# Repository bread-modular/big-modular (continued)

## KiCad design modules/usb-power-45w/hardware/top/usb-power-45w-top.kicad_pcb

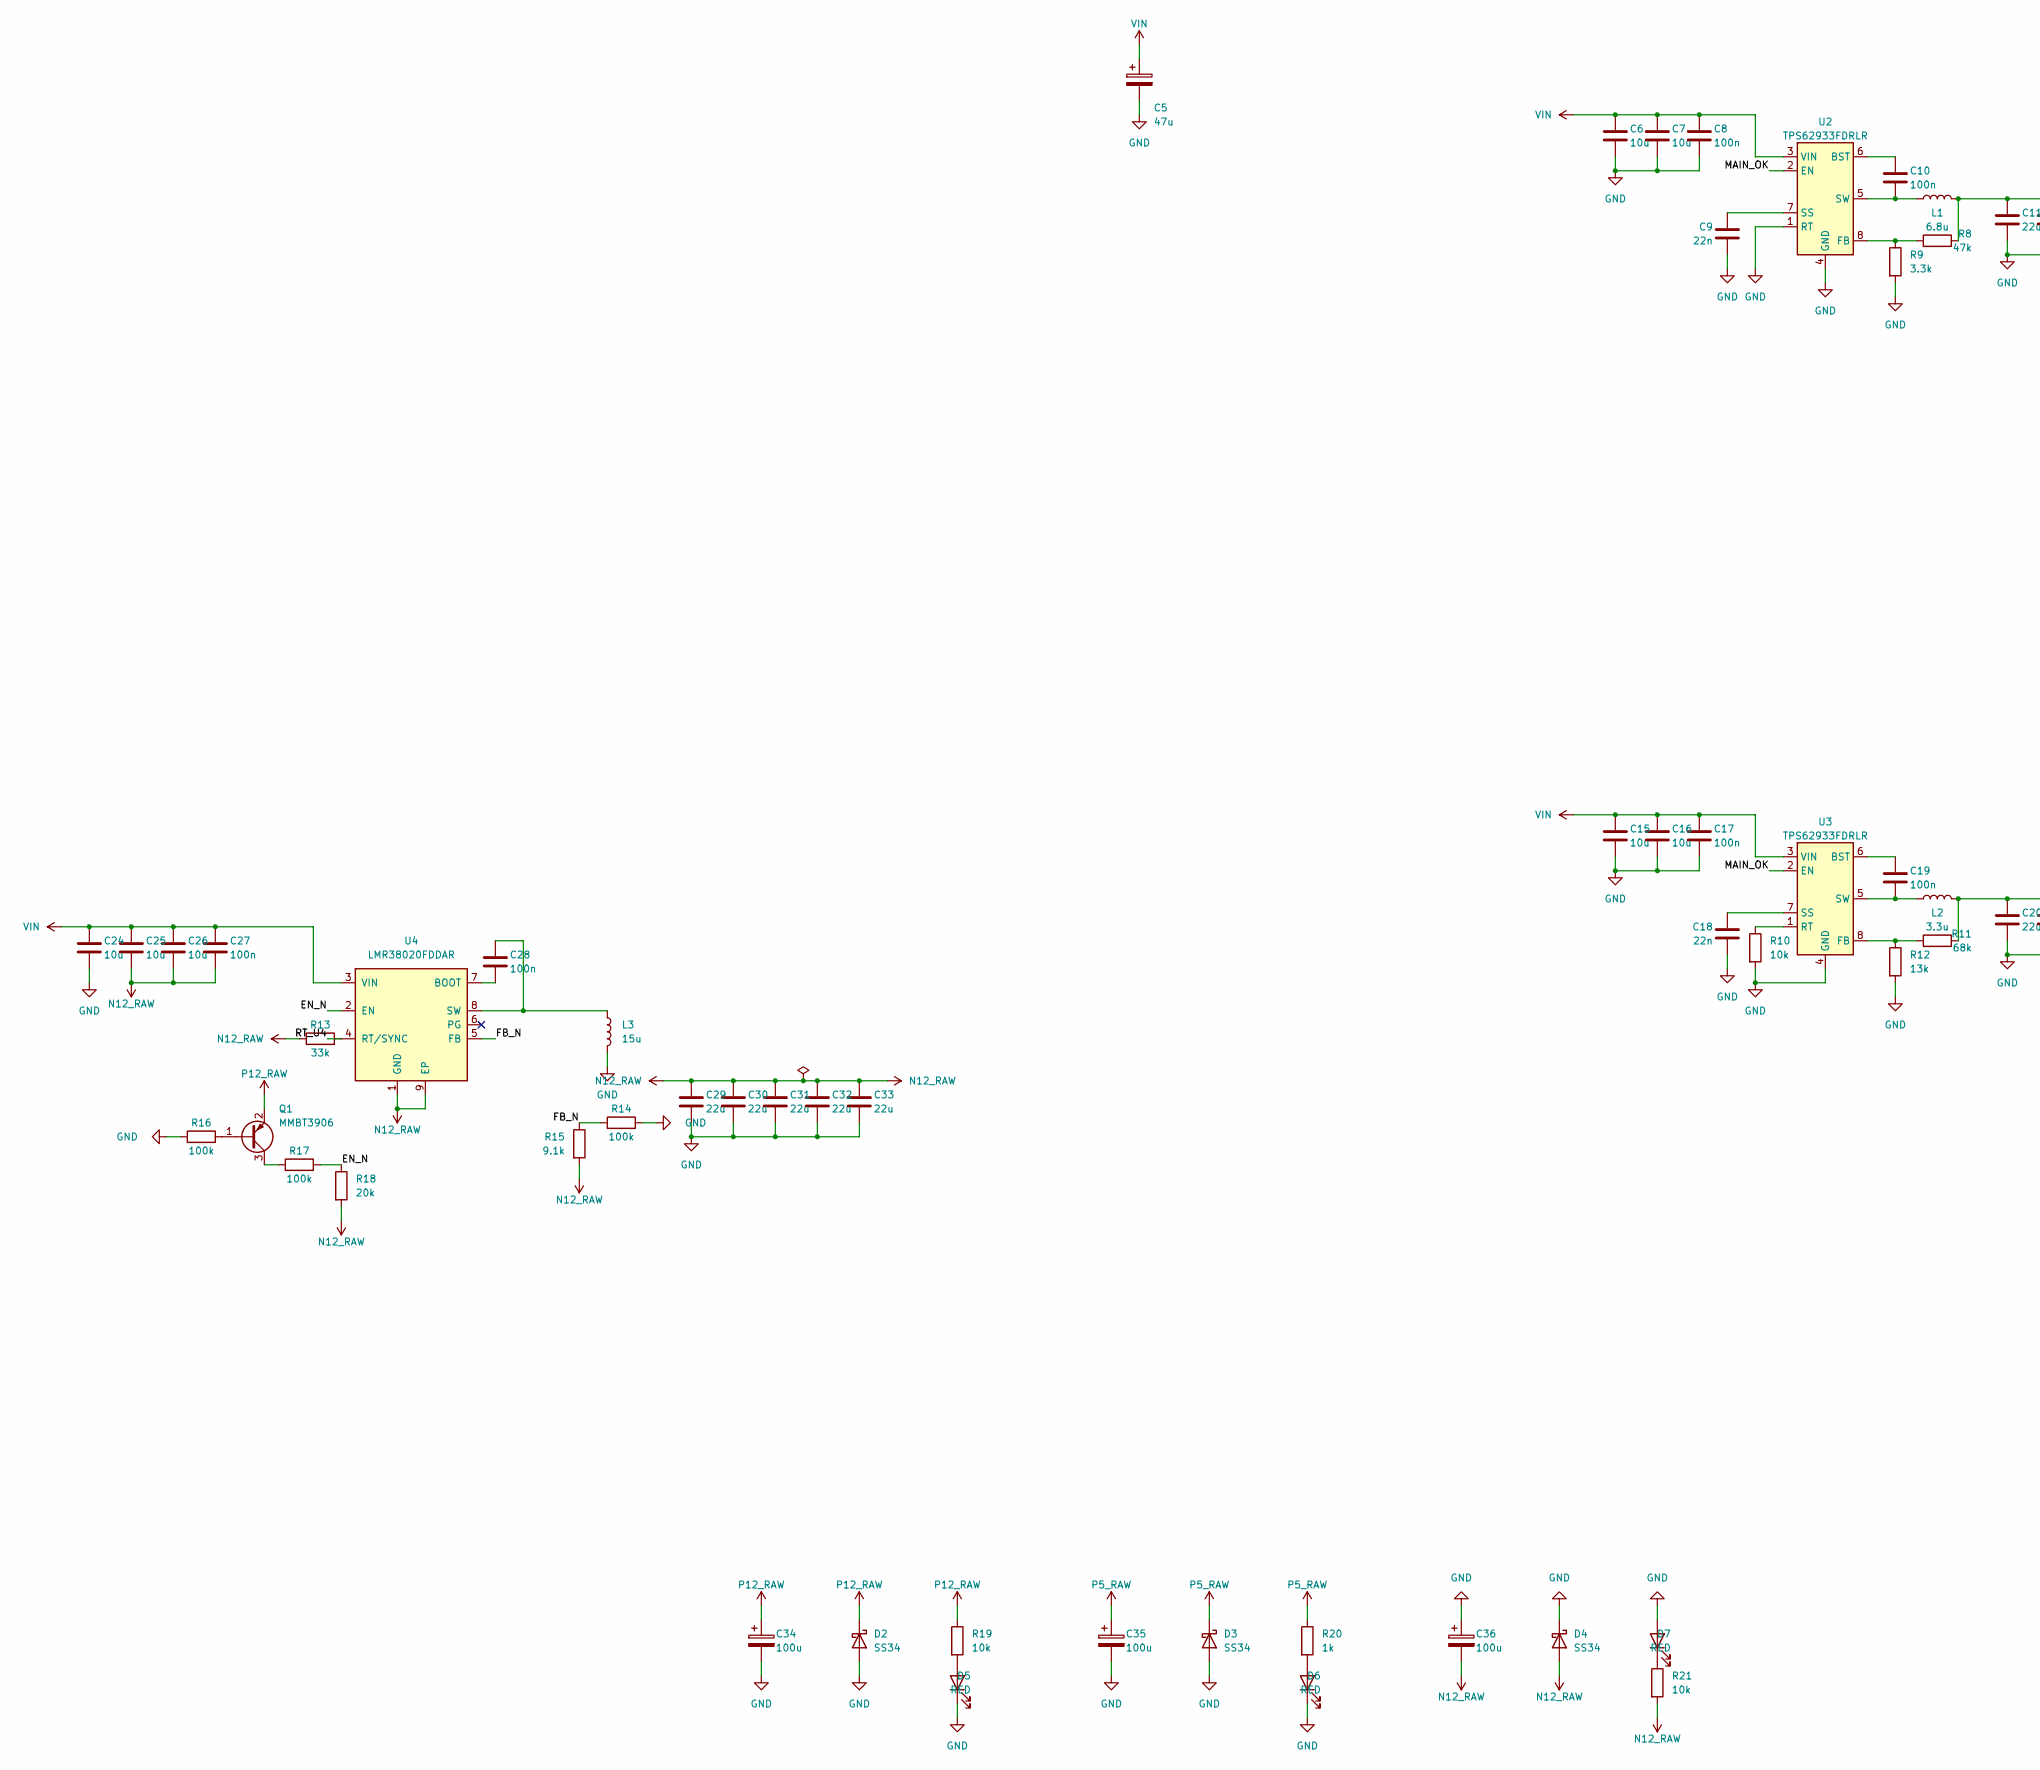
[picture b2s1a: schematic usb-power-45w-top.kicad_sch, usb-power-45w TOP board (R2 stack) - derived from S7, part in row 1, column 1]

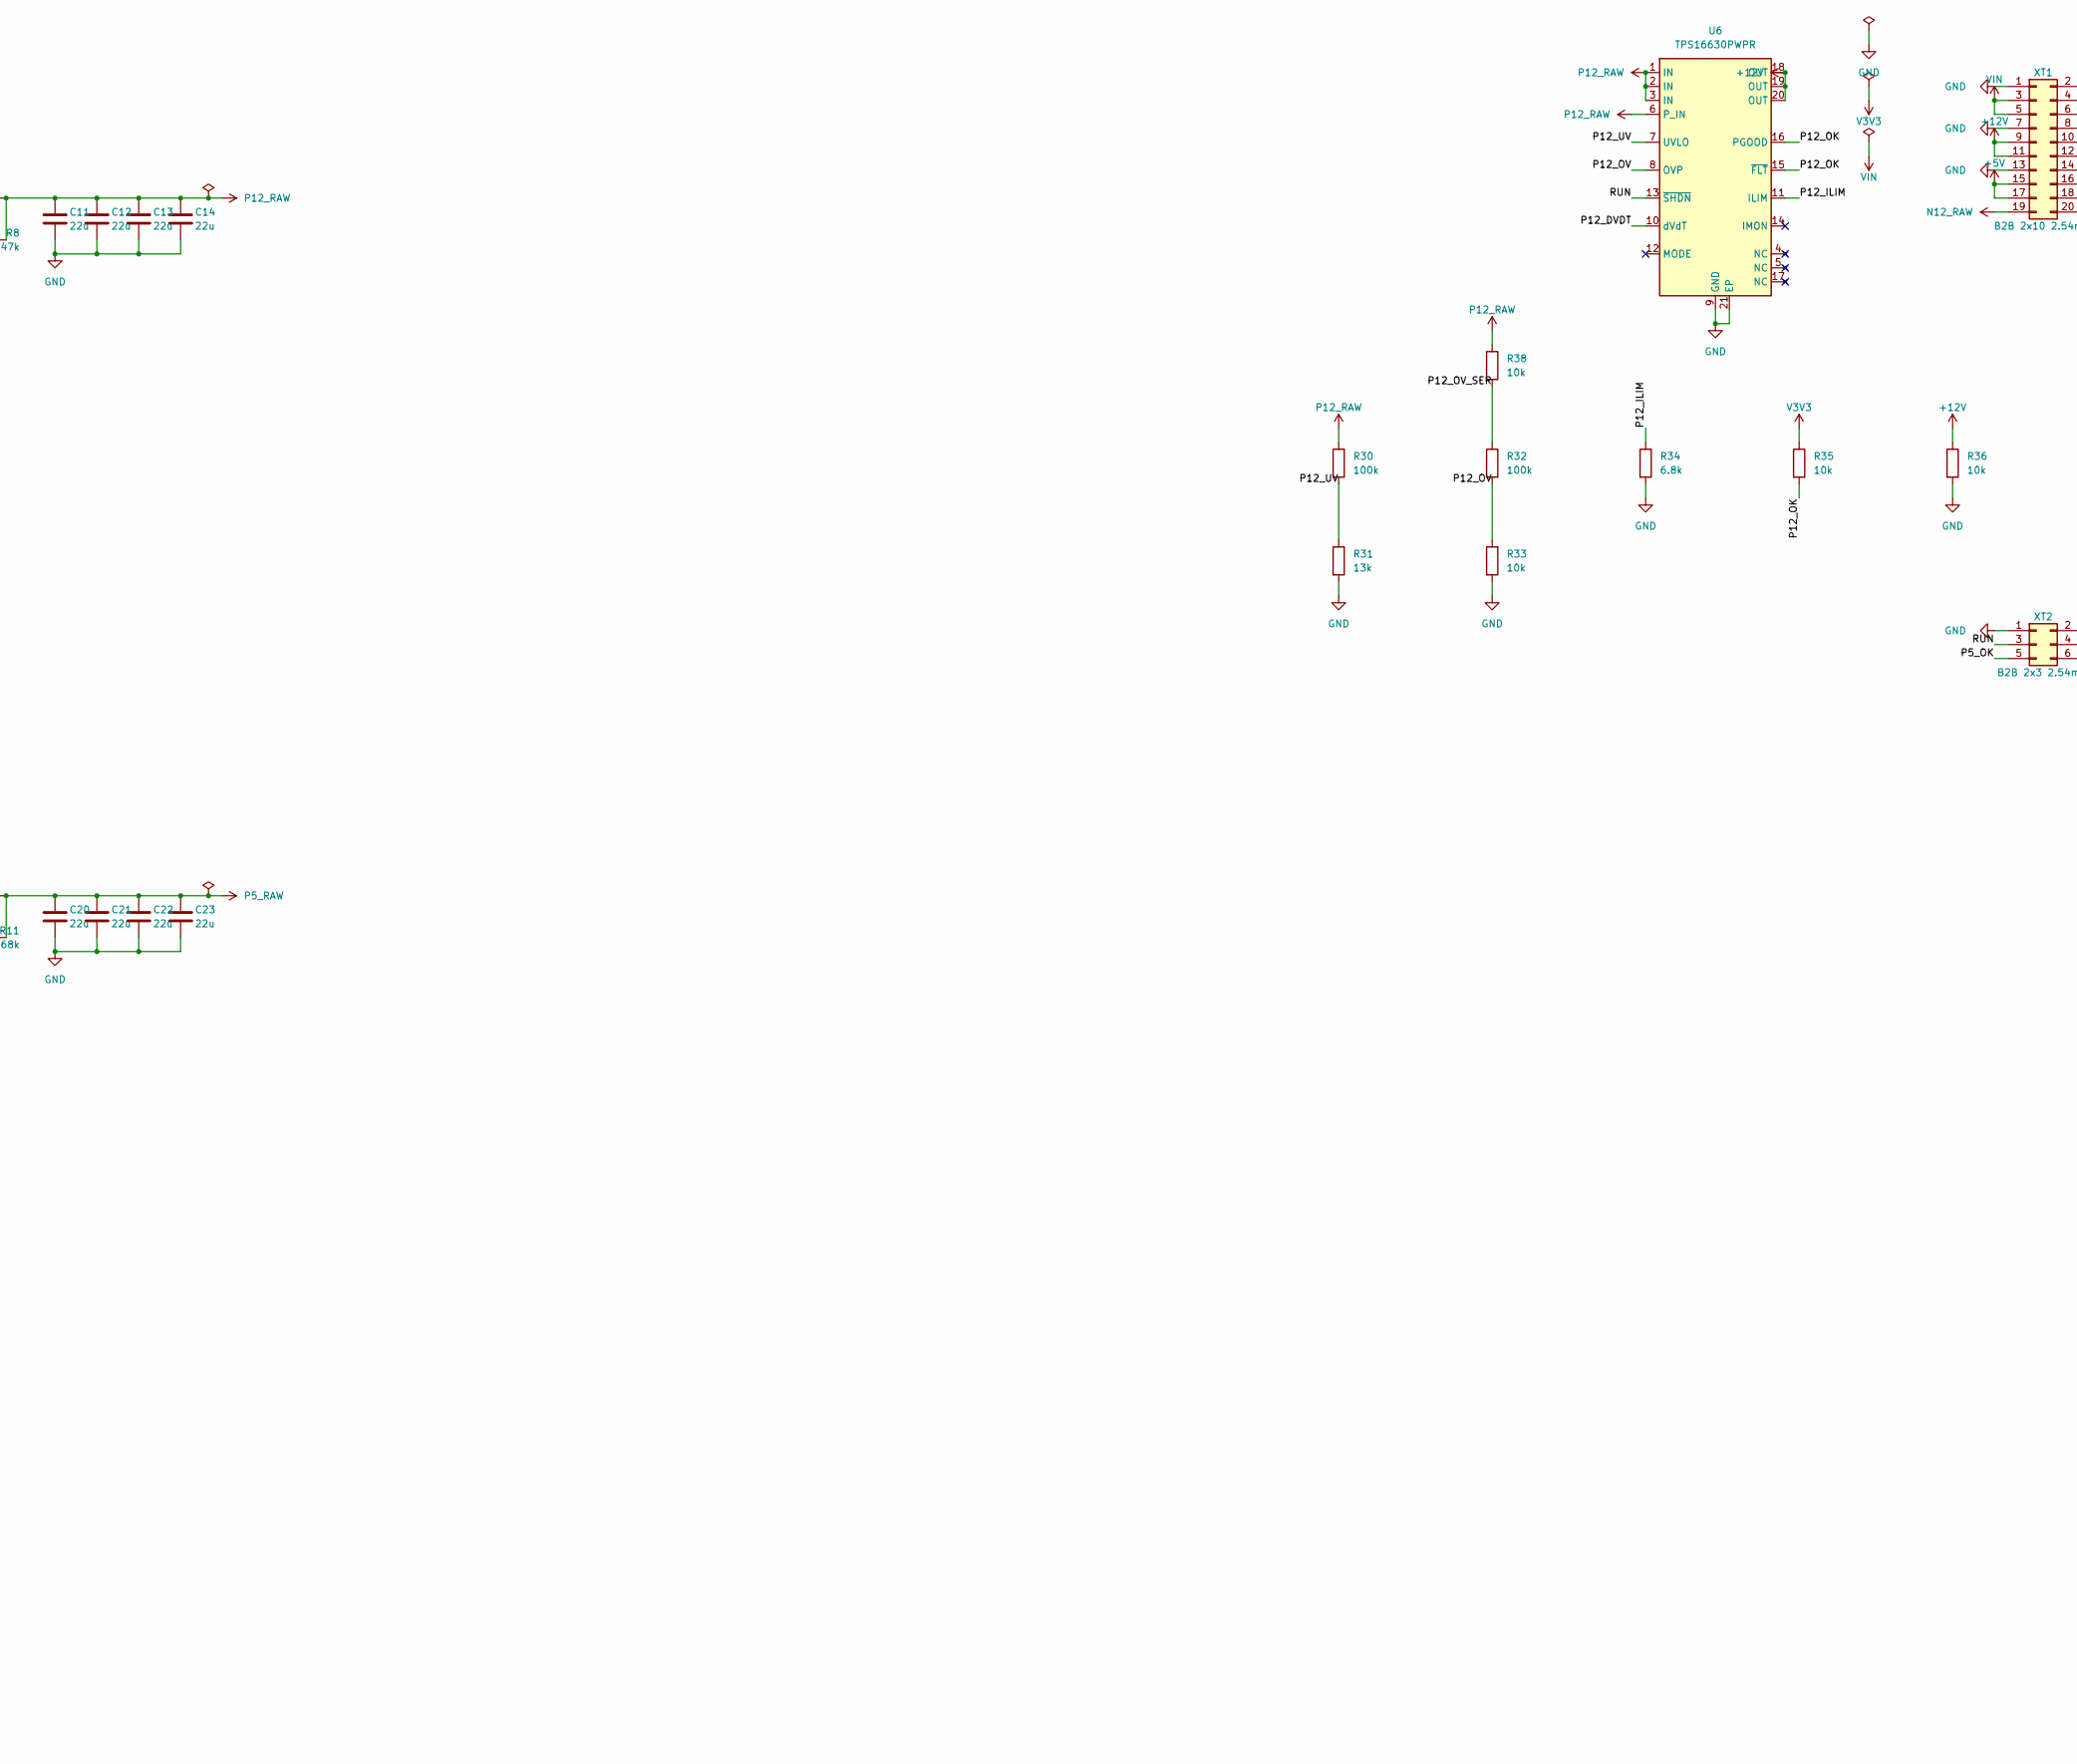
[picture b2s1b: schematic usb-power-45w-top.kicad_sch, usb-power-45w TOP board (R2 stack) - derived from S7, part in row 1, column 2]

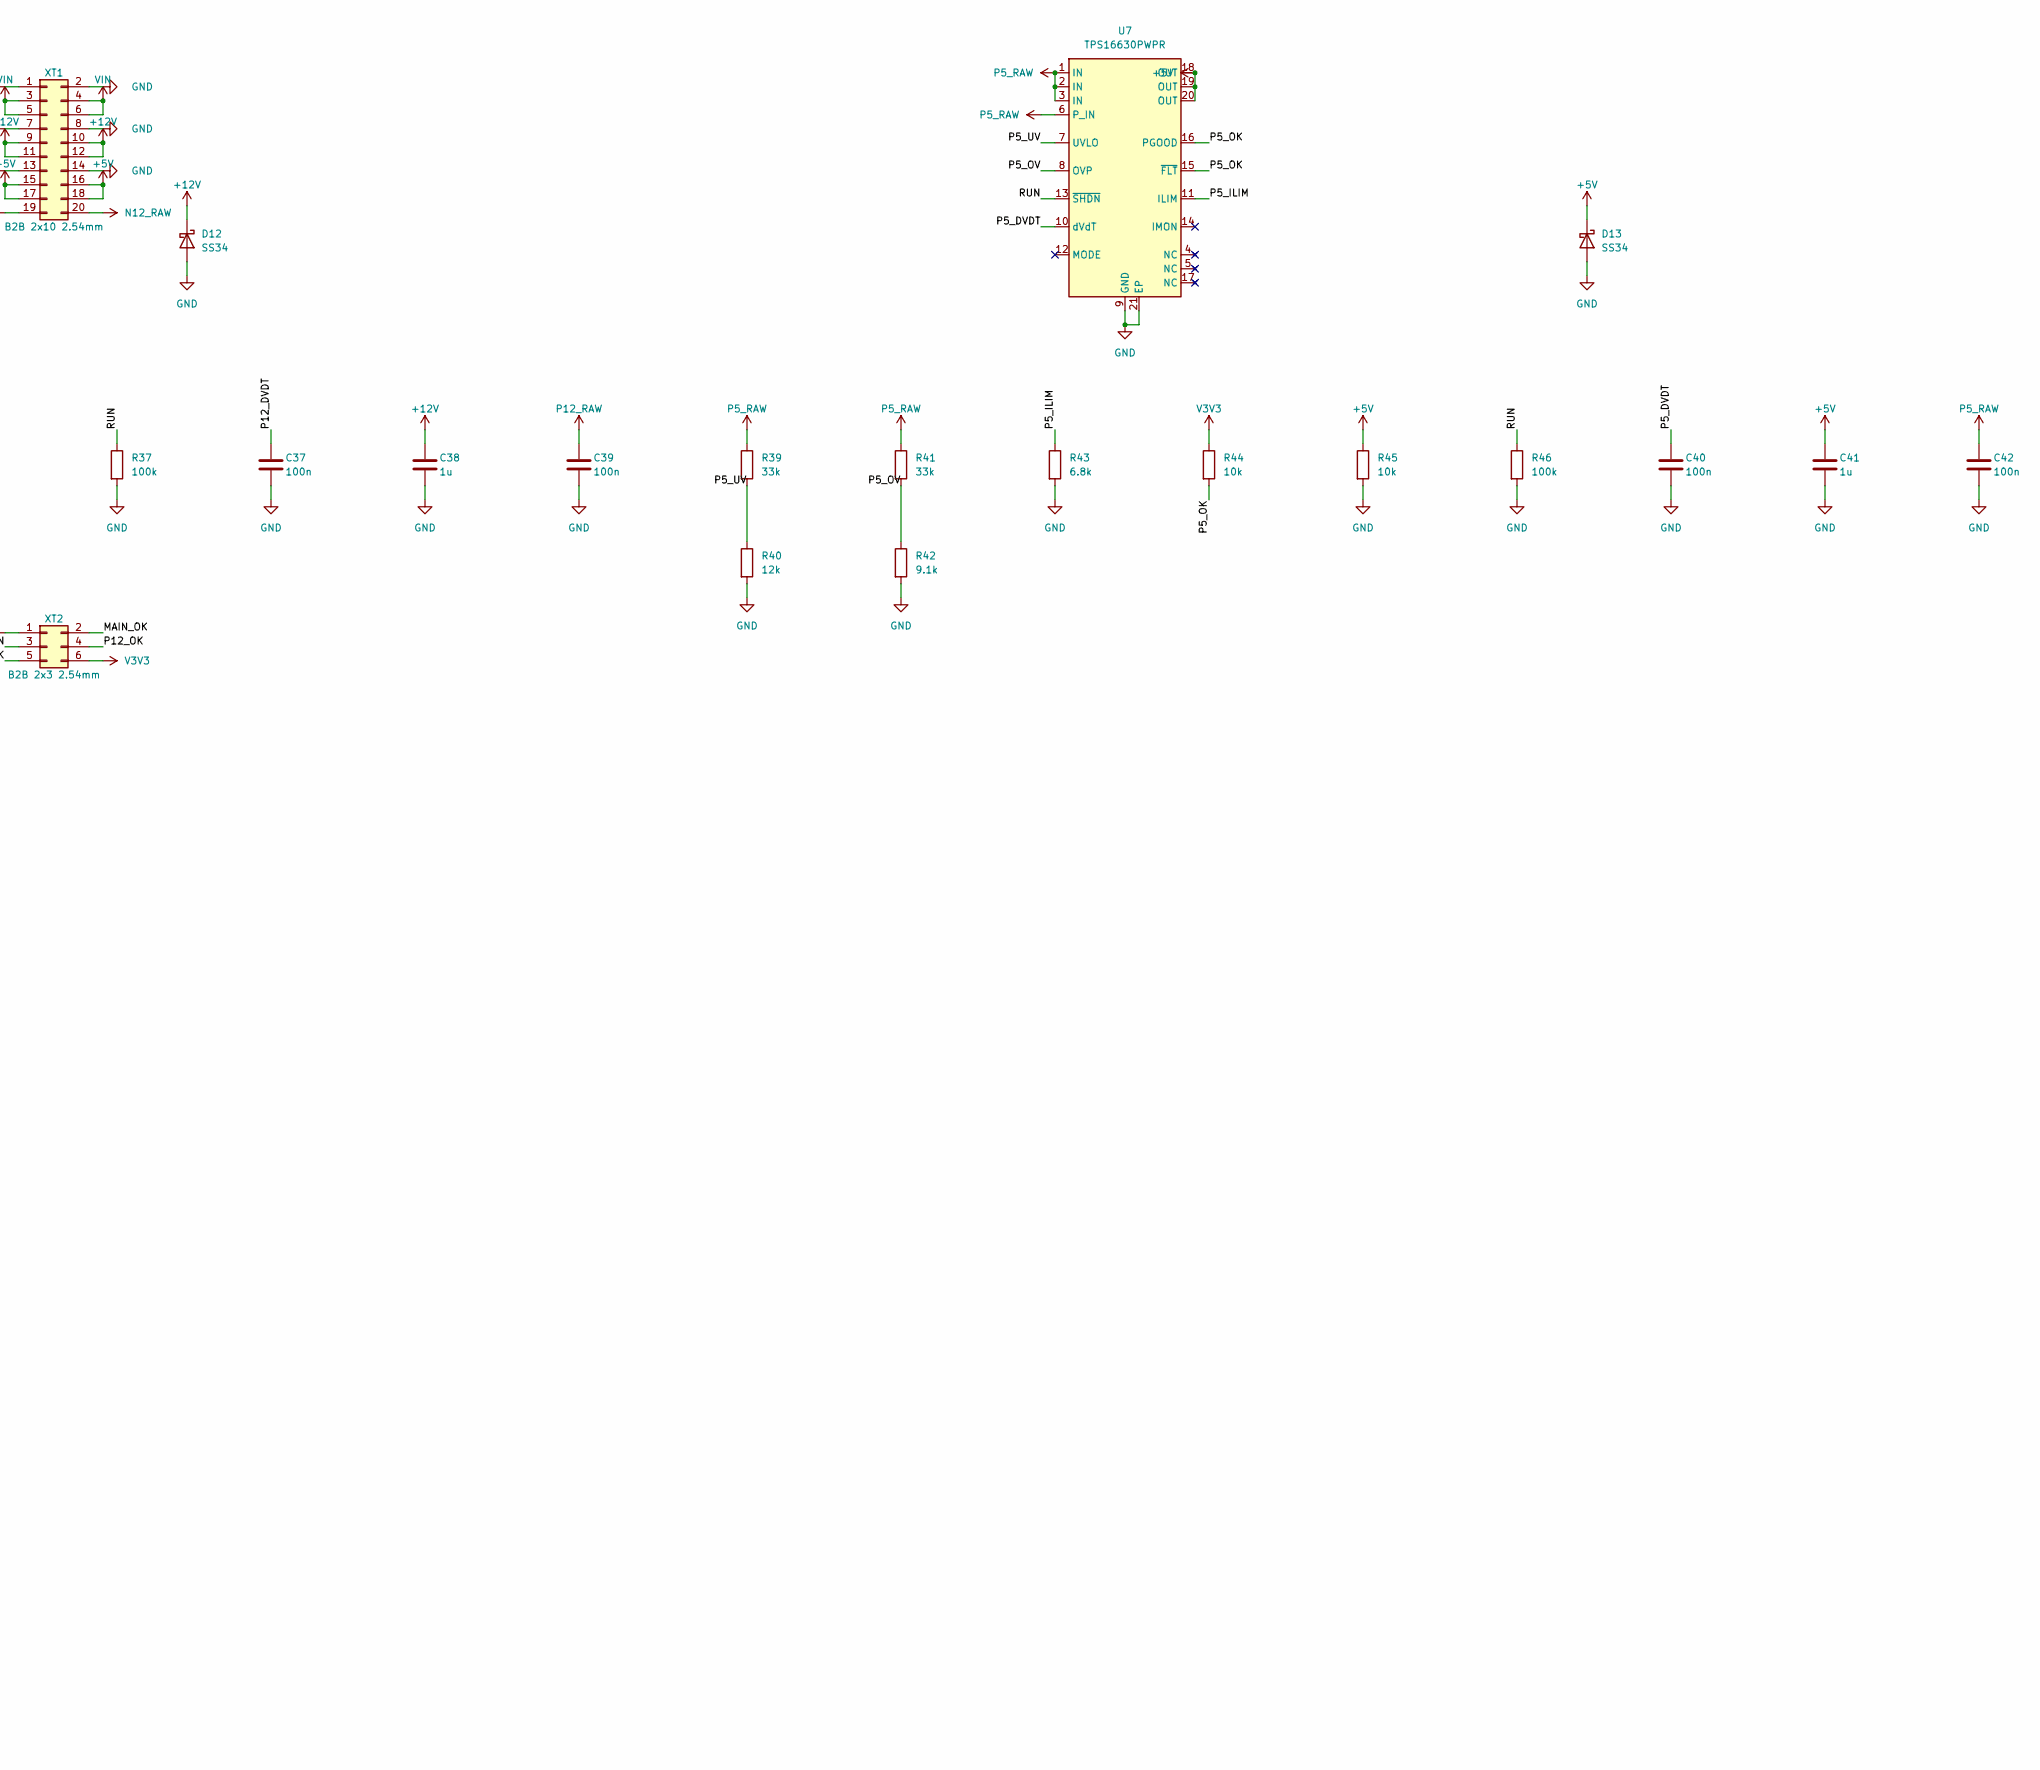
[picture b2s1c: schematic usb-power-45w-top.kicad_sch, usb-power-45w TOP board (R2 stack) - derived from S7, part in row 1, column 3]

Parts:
C5: 47u; CP_Elec_6.3x7.7; Voltage 50V; MPN MVK50V47M6.3*8 6.3TP; LCSC C165527
C6, C7, C15, C16, C24, C25, C26: 10u; C_1206_3216Metric; Voltage 50V; MPN CL31A106KBHNNNE; LCSC C13585
C8, C10, C17, C19, C27, C28, C37, C39, C40, C42: 100n; C_0603_1608Metric; Voltage 50V; MPN CC0603KRX7R9BB104; LCSC C14663
C9, C18: 22n; C_0603_1608Metric; Voltage 50V; MPN CL10B223KB8NNNC; LCSC C21122
C11, C12, C13, C14, C20, C21, C22, C23, C29, C30, C31, C32, C33: 22u; C_1206_3216Metric; Voltage 25V; MPN CL31A226KAHNNNE; LCSC C12891
C34, C35, C36: 100u; CP_Elec_6.3x7.7; Voltage 35V; MPN MVK 35V100 M 6.3*8; LCSC C350012
C38, C41: 1u; C_0603_1608Metric; Voltage 50V; MPN CL10A105KB8NNNC; LCSC C15849
D2, D3, D4, D12, D13: SS34; D_SMA; MPN SS34; LCSC C8678
D5, D6, D7: RED; LED_0603_1608Metric; MPN KT-0603R; LCSC C2286
L1: 6.8u; L_SLO1040H6R8MTT; MPN SLO1040H6R8MTT; LCSC C207852
L2: 3.3u; L_SLO1040H6R8MTT; MPN SLO1040H3R3MTT; LCSC C207850
L3: 15u; L_SLO1040H6R8MTT; MPN SLO1040H150MTT; LCSC C182184
Q1: MMBT3906; SOT-23; MPN MMBT3906LT1G; LCSC C53444
R8: 47k; R_0603_1608Metric; Tolerance 1%; MPN 0603WAF4702T5E; LCSC C25819
R9: 3.3k; R_0603_1608Metric; Tolerance 1%; MPN 0603WAF3301T5E; LCSC C22978
R10, R19, R21, R33, R35, R36, R38, R44, R45: 10k; R_0603_1608Metric; Tolerance 1%; MPN 0603WAF1002T5E; LCSC C25804
R11: 68k; R_0603_1608Metric; Tolerance 1%; MPN 0603WAF6802T5E; LCSC C23231
R12, R31: 13k; R_0603_1608Metric; Tolerance 1%; MPN 0603WAF1302T5E; LCSC C22797
R13, R39, R41: 33k; R_0603_1608Metric; Tolerance 1%; MPN 0603WAF3302T5E; LCSC C4216
R14, R16, R17, R30, R32, R37, R46: 100k; R_0603_1608Metric; Tolerance 1%; MPN 0603WAF1003T5E; LCSC C25803
R15, R42: 9.1k; R_0603_1608Metric; Tolerance 1%; MPN 0603WAF9101T5E; LCSC C23260
R18: 20k; R_0603_1608Metric; Tolerance 1%; MPN 0603WAF2002T5E; LCSC C4184
R20: 1k; R_0603_1608Metric; Tolerance 1%; MPN 0603WAF1001T5E; LCSC C21190
R34, R43: 6.8k; R_0603_1608Metric; Tolerance 1%; MPN 0603WAF6801T5E; LCSC C23212
R40: 12k; R_0603_1608Metric; Tolerance 1%; MPN 0603WAF1202T5E; LCSC C22790
U2, U3: TPS62933FDRLR; SOT-583-8; MPN TPS62933FDRLR; LCSC C5219272
U4: LMR38020FDDAR; TI_SO-PowerPAD-8_ThermalVias; MPN LMR38020FDDAR; LCSC C5149193
U6, U7: TPS16630PWPR; HTSSOP-20-1EP_4.4x6.5mm_P0.65mm_EP3.4x6.5mm_Mask2.96x2.96mm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; MPN TPS16630PWPR; LCSC C1849461
XT1: B2B 2x10 2.54mm; PinHeader_2x10_P2.54mm_Vertical; MPN TSW-110-07-G-D
XT2: B2B 2x3 2.54mm; PinHeader_2x03_P2.54mm_Vertical; MPN TSW-103-07-G-D

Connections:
+5V: C41.1, D13.1 (K), R45.1, U7.18 (OUT), U7.19 (OUT), U7.20 (OUT), XT1.15, XT1.16, XT1.17, XT1.18
+12V: C38.1, D12.1 (K), R36.1, U6.18 (OUT), U6.19 (OUT), U6.20 (OUT), XT1.9, XT1.10, XT1.11, XT1.12
/EN_N: R17.2, R18.1, U4.2 (EN)
/FB_N: R14.1, R15.1, U4.5 (FB)
/MAIN_OK: U2.2 (EN), U3.2 (EN), XT2.2
/P5_DVDT: C40.1, U7.10 (dVdT)
/P5_ILIM: R43.1, U7.11 (ILIM)
/P5_OK: R44.2, U7.15 (~FLT), U7.16 (PGOOD), XT2.5
/P5_OV: R41.2, R42.1, U7.8 (OVP)
/P5_UV: R39.2, R40.1, U7.7 (UVLO)
/P12_DVDT: C37.1, U6.10 (dVdT)
/P12_ILIM: R34.1, U6.11 (ILIM)
/P12_OK: R35.2, U6.15 (~FLT), U6.16 (PGOOD), XT2.4
/P12_OV: R32.2, R33.1, U6.8 (OVP)
/P12_OV_SER: R32.1, R38.2
/P12_UV: R30.2, R31.1, U6.7 (UVLO)
/RT_U4: R13.2, U4.4 (RT/SYNC)
/RUN: R37.1, R46.1, U6.13 (~SHDN), U7.13 (~SHDN), XT2.3
GND: C5.2, C6.2, C7.2, C8.2, C9.2, C11.2, C12.2, C13.2, C14.2, C15.2, C16.2, C17.2, C18.2, C20.2, C21.2, C22.2, C23.2, C24.2, C29.2, C30.2, C31.2, C32.2, C33.2, C34.2, C35.2, C36.1, C37.2, C38.2, C39.2, C40.2, C41.2, C42.2, D2.2 (A), D3.2 (A), D4.1 (K), D5.1 (K), D6.1 (K), D7.2 (A), D12.2 (A), D13.2 (A), L3.2, R9.2, R10.2, R12.2, R14.2, R16.1, R31.2, R33.2, R34.2, R36.2, R37.2, R40.2, R42.2, R43.2, R45.2, R46.2, U2.1 (RT), U2.4 (GND), U3.4 (GND), U6.9 (GND), U6.21 (EP), U7.9 (GND), U7.21 (EP), XT1.1, XT1.2, XT1.7, XT1.8, XT1.13, XT1.14, XT2.1
N12_RAW: C25.2, C26.2, C27.2, C29.1, C30.1, C31.1, C32.1, C33.1, C36.2, D4.2 (A), R13.1, R15.2, R18.2, R21.2, U4.1 (GND), U4.9 (EP), XT1.19, XT1.20
unnamed: D5.2 (A), R19.2
unnamed: D6.2 (A), R20.2
unnamed: D7.1 (K), R21.1
unnamed: Q1.1 (B), R16.2
unnamed: Q1.3 (C), R17.1
unnamed: C10.1, U2.6 (BST)
unnamed: R8.1, R9.1, U2.8 (FB)
unnamed: C9.1, U2.7 (SS)
unnamed: C10.2, L1.1, U2.5 (SW)
unnamed: C19.1, U3.6 (BST)
unnamed: R11.1, R12.1, U3.8 (FB)
unnamed: R10.1, U3.1 (RT)
unnamed: C18.1, U3.7 (SS)
unnamed: C19.2, L2.1, U3.5 (SW)
unnamed: C28.2, U4.7 (BOOT)
unnamed: C28.1, L3.1, U4.8 (SW)
P5_RAW: C20.1, C21.1, C22.1, C23.1, C35.1, C42.1, D3.1 (K), L2.2, R11.2, R20.1, R39.1, R41.1, U7.1 (IN), U7.2 (IN), U7.3 (IN), U7.6 (P_IN)
P12_RAW: C11.1, C12.1, C13.1, C14.1, C34.1, C39.1, D2.1 (K), L1.2, Q1.2 (E), R8.2, R19.1, R30.1, R38.1, U6.1 (IN), U6.2 (IN), U6.3 (IN), U6.6 (P_IN)
V3V3: R35.1, R44.1, XT2.6
VIN: C5.1, C6.1, C7.1, C8.1, C15.1, C16.1, C17.1, C24.1, C25.1, C26.1, C27.1, U2.3 (VIN), U3.3 (VIN), U4.3 (VIN), XT1.3, XT1.4, XT1.5, XT1.6

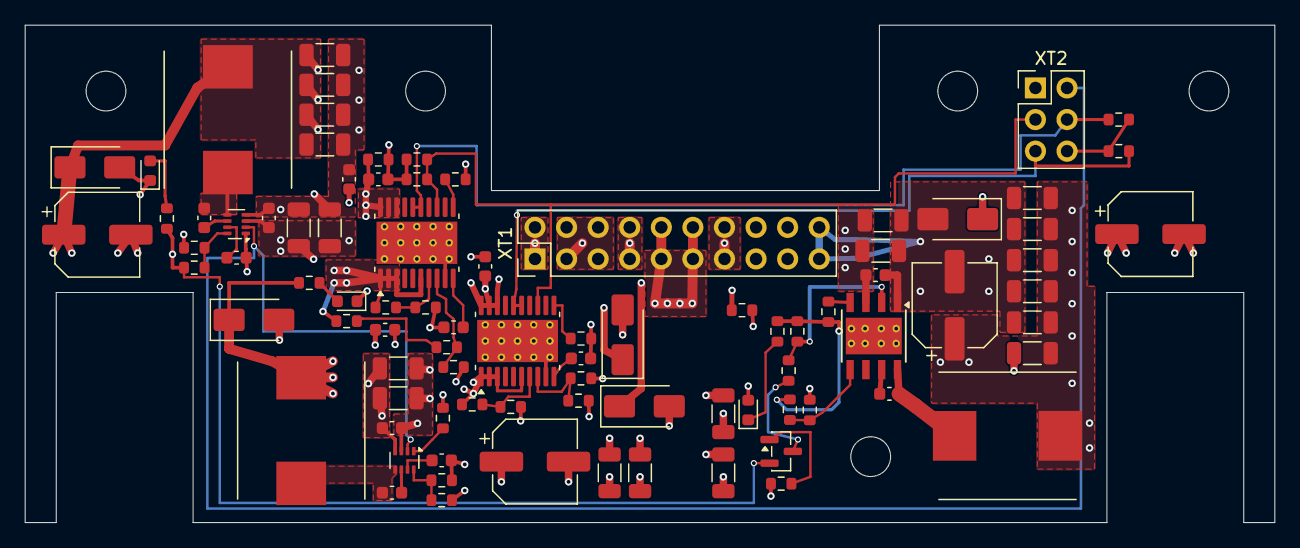
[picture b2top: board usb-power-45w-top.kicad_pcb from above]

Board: 4 copper layers, 100.5 x 40.0 mm, 88 parts (0 on the bottom side), 40 nets.

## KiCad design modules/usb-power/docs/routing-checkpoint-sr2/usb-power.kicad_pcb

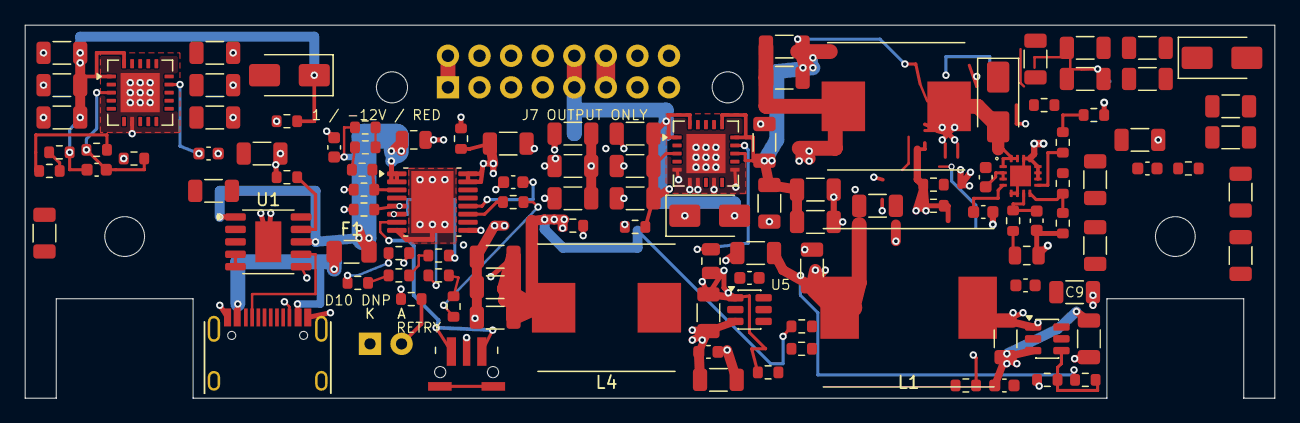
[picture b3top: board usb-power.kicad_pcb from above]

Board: 4 copper layers, 100.5 x 30.0 mm, 116 parts (0 on the bottom side), 50 nets.

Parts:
C1, C60, C86: 1u 50V X7R; C_0805_2012Metric
C2, C3, C7, C20, C35, C36, C61, C85, C88: 100n 50V X7R; C_0603_1608Metric
C4: 10u 50V X5R; C_1206_3216Metric
C5, C6, C9, C18, C19, C37, C38, C48, C49, C50, C51, C52, C53, C54, C55, C56, C57, C58, C59, C63, C64, C65, C66, C67, C68, C69, C70, C71, C72, C73, C74, C75, C76, C77, C78, C79, C80, C82, C83, C84: 22u 25V X5R; C_1206_3216Metric
C62: 10n 50V X7R; C_0603_1608Metric
C87: 100p 50V C0G; C_0603_1608Metric
C89, C90, C91, C92: 2.2u 50V X7R; C_1206_3216Metric
C93: DNP CFF / TBD; C_0603_1608Metric
D10: RED 3mm / +5V POWER / DNP; LED_D3.0mm_Horizontal_O1.27mm_Z2.0mm_Edge
D27, D28, D29, D30: SS34 40V; D_SMA
F1: 3A 32V candidate; Fuse_1206_3216Metric
J1: TYPE-C-31-M-12; HRO-TYPE-C-31-M-12
J7: Manual IDC wire landing; WireLanding_2x08_P2.54mm
L1: 22uH 20% shielded; L_TMPC1205HP_220M
L4, L5: 6.8uH 20% shielded; L_SLO1040H6R8MTT
R2: 6.8k 1%; R_0603_1608Metric
R4: 470k 1%; R_0603_1608Metric
R5, R7, R17, R81, R88, R91: 100k 1%; R_0603_1608Metric
R6: 806k 1%; R_0603_1608Metric
R8: 5.6k 1%; R_0603_1608Metric
R9, R86: 100k 0.1%; R_0603_1608Metric
R10, R74, R87: 10k 0.1%; R_0603_1608Metric
R15: 120k 0.1%; R_0603_1608Metric
R18: 13k 1%; R_0603_1608Metric
R25, R26, R27, R31, R78: 10k 1%; R_0603_1608Metric
R32: 1k 1%; R_0603_1608Metric
R36: 300k 1%; R_0603_1608Metric
R72: 90.9k 0.1%; R_0603_1608Metric
R73: 1.2k 1%; R_0603_1608Metric
R77: 82k 1%; R_0603_1608Metric
R79, R80: 220 1%; R_0603_1608Metric
R82, R93: 2k 1%; R_0603_1608Metric
R83: 0 1%; R_0603_1608Metric
R84: 6.2k 1%; R_0603_1608Metric
R85: 510 1%; R_0603_1608Metric
R89: 470 1%; R_0603_1608Metric
R90, R92: 20k 1%; R_0603_1608Metric
SW1: TL3340AF160QG; SW_TL3340AF160QG_HandSolder
U1: CH224A; SSOP-10-1EP_3.9x4.9mm_P1mm_EP2.1x3.3mm
U2: TPS26600PWPR; HTSSOP-16-1EP_4.4x5mm_P0.65mm_EP3.4x5mm_Mask2.66x2.46mm
U3, U5: TPS54302DDCR; SOT-23-6
U12: TPS7A4700RGWR; Texas_RGW0020A_VQFN-20-1EP_5x5mm_P0.65mm_EP3.15x3.15mm
U13: TPS7A3301RGWR; Texas_RGW0020A_VQFN-20-1EP_5x5mm_P0.65mm_EP3.15x3.15mm
U14: TPS55340RTER; Texas_RTE0016C_WQFN-16-1EP_3x3mm_P0.5mm_EP1.68x1.68mm

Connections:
/Autonomous hardware window and retry/EF_MODE: R36.1, U2.6 (MODE)
/Autonomous hardware window and retry/EF_SHDN: SW1.1 (COMMON), SW1.3 (COMMON), U2.7 (SHDN)
/Autonomous hardware window and retry/ILIM: R8.1, U2.11 (ILIM)
/Autonomous hardware window and retry/ILIM_SER_1: R8.2, R79.1
/Autonomous hardware window and retry/ILIM_SER_2: R79.2, R80.1
/Autonomous hardware window and retry/MODE_SER_1: R36.2, R81.1
/Autonomous hardware window and retry/MODE_SER_2: R81.2, R82.1
/Autonomous hardware window and retry/OV_SET: R6.2, R7.1, U2.5 (OVP)
/Autonomous hardware window and retry/RTN: C3.2, R5.2, R7.2, R80.2, R82.2, SW1.2 (NO), U2.8 (RTN), U2.17 (EP_RTN)
/Autonomous hardware window and retry/SLEW: C3.1, U2.12 (dVdT)
/Autonomous hardware window and retry/UV_EN: R5.1, R78.2, U2.3 (UVLO)
/Autonomous hardware window and retry/UV_SER_1: R4.2, R77.1
/Autonomous hardware window and retry/UV_SER_2: R77.2, R78.1
/Board output and power LED/LED_P_A: D10.2 (A), R32.2
/Direct 9V negative IBB/NINV_BOOT: C35.1, U3.6 (BOOT)
/Direct 9V negative IBB/NINV_DIV1: R9.2, R15.1
/Direct 9V negative IBB/NINV_DIV2: R15.2, R84.1
/Direct 9V negative IBB/NINV_EN: R91.2, R92.1, U3.5 (EN)
/Direct 9V negative IBB/NINV_EN_LO: R92.2, R93.1
/Direct 9V negative IBB/NINV_FB: C93.2, R10.1, R84.2, U3.4 (FB)
/Direct 9V negative IBB/NINV_SW: C35.2, L1.1, U3.2 (SW)
/Direct 9V negative IBB/NRAW: C6.1, C7.2, C9.1, C37.1, C54.1, C55.1, C56.1, C67.1, C70.1, C71.1, C74.1, C75.1, C76.1, C89.2, C90.2, C91.2, C92.2, D28.2 (A), D30.2 (A), R10.2, R93.2, U3.1 (GND), U13.13 (EN), U13.15 (IN), U13.16 (IN)
/Direct 9V positive boost/PBOOST_COMP: C87.1, R89.1, U14.7 (COMP)
/Direct 9V positive boost/PBOOST_COMP_RC: C86.1, R89.2
/Direct 9V positive boost/PBOOST_FB: R86.2, R87.1, U14.8 (FB)
/Direct 9V positive boost/PBOOST_FREQ: R88.1, U14.9 (FREQ)
/Direct 9V positive boost/PBOOST_FREQ_SER: R88.2, R90.1
/Direct 9V positive boost/PBOOST_SS: C85.1, U14.4 (SS)
/Direct 9V positive boost/PBOOST_SW: D29.2 (A), L5.2, U14.1 (SW), U14.15 (SW), U14.16 (SW)
/Direct 9V positive boost/PRAW: C48.1, C49.1, C50.1, C63.1, C77.1, C78.1, C79.1, C80.1, D27.1 (K), D29.1 (K), R86.1, U12.13 (EN), U12.15 (IN), U12.16 (IN)
/GND: C1.2, C2.2, C4.2, C5.2, C6.2, C9.2, C18.2, C19.2, C20.2, C37.2, C38.2, C48.2, C49.2, C50.2, C51.2, C52.2, C53.2, C54.2, C55.2, C56.2, C57.2, C58.2, C59.2, C60.2, C61.2, C63.2, C64.2, C65.2, C66.2, C67.2, C68.2, C69.2, C70.2, C71.2, C72.2, C73.2, C74.2, C75.2, C76.2, C77.2, C78.2, C79.2, C80.2, C82.2, C83.2, C84.2, C85.2, C86.2, C87.2, C88.2, C93.1, D10.1 (K), D30.1 (K), J1.A1 (GND), J1.A12 (GND), J1.S1 (SHIELD), J7.3, J7.4, J7.5, J7.6, J7.7, J7.8, L1.2, R2.2, R9.1, R25.2, R26.2, R27.2, R31.2, R74.2, R85.2, R87.2, R90.2, U1.11 (EP0_GND), U2.9 (GND), U5.1 (GND), U12.5 (6P4V1), U12.6 (3P2V), U12.7 (GND), U12.9 (0P8V), U12.11 (0P2V), U12.21 (EP_GND), U13.7 (GND), U13.21 (EP_GND), U14.5 (SYNC), U14.6 (AGND), U14.10 (RSVD_GND), U14.11 (PGND), U14.12 (PGND), U14.13 (PGND), U14.14 (RSVD_GND), U14.17 (EP_AGND)
/Independent +5V buck/FIVE_BOOT: C36.1, U5.6 (BOOT)
/Independent +5V buck/FIVE_DIV_LO: R18.2, R85.1
/Independent +5V buck/FIVE_FB: R17.2, R18.1, U5.4 (FB)
/Independent +5V buck/FIVE_SW: C36.2, L4.1, U5.2 (SW)
/N12: C57.1, C58.1, C59.1, C62.1, C73.1, D28.1 (K), J7.1, J7.2, R26.1, R72.1, U13.1 (OUT), U13.20 (OUT)
/P5: C19.1, C38.1, C72.1, J7.11, J7.12, L4.2, R17.1, R27.1, R32.1
/P12: C51.1, C52.1, C53.1, C64.1, C65.1, C66.1, D27.2 (A), J7.9, J7.10, R25.1, U12.1 (OUT), U12.3 (SENSE), U12.20 (OUT)
/Quiet bipolar post-regulators/N_LDO_DIV: R73.1, R83.2
/Quiet bipolar post-regulators/N_LDO_FB: C62.2, R73.2, R74.1, U13.3 (FB)
/Quiet bipolar post-regulators/N_LDO_SER: R72.2, R83.1
/Quiet bipolar post-regulators/N_NR: C61.1, U13.14 (NR/SS)
/Quiet bipolar post-regulators/P_NR: C60.1, U12.14 (NR)
/USB PD input/CC1: J1.A5 (CC1), U1.7 (CC1)
/USB PD input/CC2: J1.B5 (CC2), U1.6 (CC2)
/USB PD input/PD_CFG: R2.1, U1.9 (CFG1)
/USB PD input/PD_D_SHORT: U1.4 (DP), U1.5 (DM)
/USB PD input/USB_VBUS: F1.1, J1.A4 (VBUS), J1.A9 (VBUS)
/VIN9: C1.1, C2.1, F1.2, R4.1, R6.1, U1.1 (VHV), U1.8 (VBUS_SENSE), U2.1 (IN), U2.2 (IN)
/VPROT: C4.1, C5.1, C7.1, C18.1, C20.1, C68.1, C69.1, C82.1, C83.1, C84.1, C88.1, C89.1, C90.1, C91.1, C92.1, L5.1, R31.1, R91.1, U2.15 (OUT), U2.16 (OUT), U3.3 (VIN), U5.3 (VIN), U14.2 (VIN), U14.3 (EN)

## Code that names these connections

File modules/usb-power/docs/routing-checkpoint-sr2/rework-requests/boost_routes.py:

#!/usr/bin/env python3
"""Explicit manually chosen boost connections -> common operations JSON.
No search/path-finding/router. Coordinates below are individually reviewed.
"""
import json
from pathlib import Path
import uuid
HERE=Path(__file__).resolve().parent
N=uuid.uuid5(uuid.NAMESPACE_URL,'usb-power/sr2-rework072/manual-boost-v1')
ops=[]
notes=[]

def pad(ref,num):return {'pad':{'ref':ref,'number':str(num)}}
def route(label,net,width,a,b,points=(),layer='F.Cu',reason=''):
    uid=str(uuid.uuid5(N,label))
    ops.append({'op':'add_polyline','uuid':uid,'net':net,'layer':layer,'width_mm':width,'start':a,'end':b,'waypoints':list(points)})
    notes.append({'label':label,'uuid':uid,'net':net,'reason':reason})
    return uid

def via(label,net,xy,diam=.65):
    uid=str(uuid.uuid5(N,label));ops.append({'op':'add_via','uuid':uid,'net':net,'at':xy,'diameter_mm':diam,'drill_mm':.3});return {'uuid':uid}

B='/Direct 9V positive boost/'
route('input-bank','/VPROT',1.2,pad('C82',1),pad('C83',1),reason='Input-bank positive spine on front copper; avoid return-pad row')
route('inductor-input','/VPROT',1.2,pad('C83',1),pad('L5',1),[[109.325,78.8]],reason='Short input-capacitor to inductor path around bank return pads')
route('switch-main',B+'PBOOST_SW',1.2,pad('L5',2),pad('D29',2),[[126.35,78.8]],reason='Wide 45-degree inductor-to-rectifier switching path; no vias')
sw=route('switch-fanout',B+'PBOOST_SW',.25,pad('U14',16),pad('D29',2),[[129.05,82.9],[128.4,82.25],[128,82.25]],reason='QFN limited-width fanout; trunk overlaid wider up to 82.25 mm')
route('switch-trunk-overlay',B+'PBOOST_SW',1.0,pad('D29',2),{'track':str(uuid.uuid5(uuid.UUID(sw),'3')),'at':[128,82.25]},reason='Widen long trunk without widening adjacent QFN pad escapes')
route('switch-pin15',B+'PBOOST_SW',.25,pad('U14',15),pad('U14',16),reason='Adjacent parallel switch pads')
route('switch-pin1',B+'PBOOST_SW',.25,pad('U14',1),pad('U14',16),[[128.4,83.0]],reason='Short left/top switch-pad tie clear of exposed grounded pad')
route('vin-decouple','/VPROT',.25,pad('C88',1),pad('U14',2),[[127.8,84.475],[127.8,84.15]],reason='Local VIN decoupler, not main inductor load-current feed')
route('enable-vin','/VPROT',.25,pad('U14',2),pad('U14',3),reason='EN tied to VIN as frozen schematic specifies')
route('soft-start',B+'PBOOST_SS',.25,pad('U14',4),pad('C85',1),[[128,85.55],[127.775,85.55]],reason='Direct quiet SS connection south/west, away from switching node')
route('comp-to-r',B+'PBOOST_COMP',.25,pad('U14',7),pad('R89',1),[[130.05,86.325],[129.2,86.325]],reason='Short analog COMP fanout south of IC')
route('comp-c',B+'PBOOST_COMP',.25,pad('R89',1),pad('C87',1),[[131.05,87.175]],reason='Local compensation C parallel at same COMP point')
route('comp-series',B+'PBOOST_COMP_RC',.25,pad('R89',2),pad('C86',1),[[129.2,90.65]],reason='Compensation series branch, no shared high-current copper')
route('fb-divider',B+'PBOOST_FB',.25,pad('R86',2),pad('R87',1),reason='Compact feedback-divider junction')
route('fb-sense',B+'PBOOST_FB',.25,pad('U14',8),pad('R86',2),[[131.05,86.3],[132.725,86.3]],reason='Dedicated feedback sense outside switch loop; output Kelvin source still to be routed')
route('freq',B+'PBOOST_FREQ',.25,pad('U14',9),pad('R88',1),[[132,85.15],[132,82.525]],reason='Frequency resistor path east of grounded IC pins, not switch pins')
route('freq-series',B+'PBOOST_FREQ_SER',.25,pad('R88',2),pad('R90',1),[[133.2,79.5]],reason='Frozen two-resistor timing network')
# Deliberate returns to the existing In1.Cu ground plane, ordinary 0.3-mm drills.
route('ep-to-pgnd','/GND',.3,pad('U14',17),pad('U14',14),reason='Local exposed-pad to power-ground tie')
route('pgnd-top','/GND',.3,pad('U14',14),pad('U14',13),reason='Top power-ground pins paired')
route('pgnd-east','/GND',.3,pad('U14',13),pad('U14',12),reason='Ground-only perimeter tie')
route('pgnd-east11','/GND',.3,pad('U14',12),pad('U14',11))
route('pgnd-east10','/GND',.3,pad('U14',11),pad('U14',10))
route('agnd-to-ep','/GND',.3,pad('U14',6),pad('U14',17),reason='Quiet analog return directly to exposed ground pad')
route('agnd-bottom','/GND',.3,pad('U14',5),pad('U14',6))
g1=via('pgnd-via1','/GND',[130.9,81.8]);g2=via('pgnd-via2','/GND',[131.65,81.8])
route('pgnd-via-feed','/GND',.5,pad('U14',13),g1,[[130.9,82.65]],reason='Two parallel ground vias near boost switch return, outside QFN lands')
route('pgnd-vias','/GND',.6,g1,g2)
route('ss-ground','/GND',.4,pad('U14',5),pad('C85',2),[[128.8,86.075]],reason='Local analog return, not daisy-chained with switch path')
g3=via('quiet-via1','/GND',[127.575,88.3])
route('ss-plane','/GND',.5,pad('C85',2),g3)
route('comp-ground','/GND',.4,pad('C87',2),pad('C86',2),[[131.1,90.65]])
route('fb-ground','/GND',.4,pad('R87',2),pad('C87',2),[[131.35,89.025]],reason='Quiet divider return through local ground, no power-loop current')
g4=via('quiet-via2','/GND',[132,90.0])
route('comp-plane','/GND',.5,pad('C86',2),g4,[[131.25,90.75]])
g5=via('freq-via','/GND',[136.525,78.5])
route('freq-ground','/GND',.4,pad('R90',2),g5)

if __name__=='__main__':
    for name,data in [('boost-001.routes.json',{'schema_version':1,'operations':ops}),('boost-001.intent.json',{'method':'manual explicit routes, no autorouter','accepted_placement_preserved':'L5 (119.8,78.8),0,F.Cu','routes':notes,'not_complete':'PRAW output/Kelvin feed, remaining input/return and negative converter routing pending; these connections alone are not a complete supply'})]:
        with (HERE/name).open('x') as f:json.dump(data,f,indent=2);f.write('\n')
    print(len(ops),'explicit operations')
